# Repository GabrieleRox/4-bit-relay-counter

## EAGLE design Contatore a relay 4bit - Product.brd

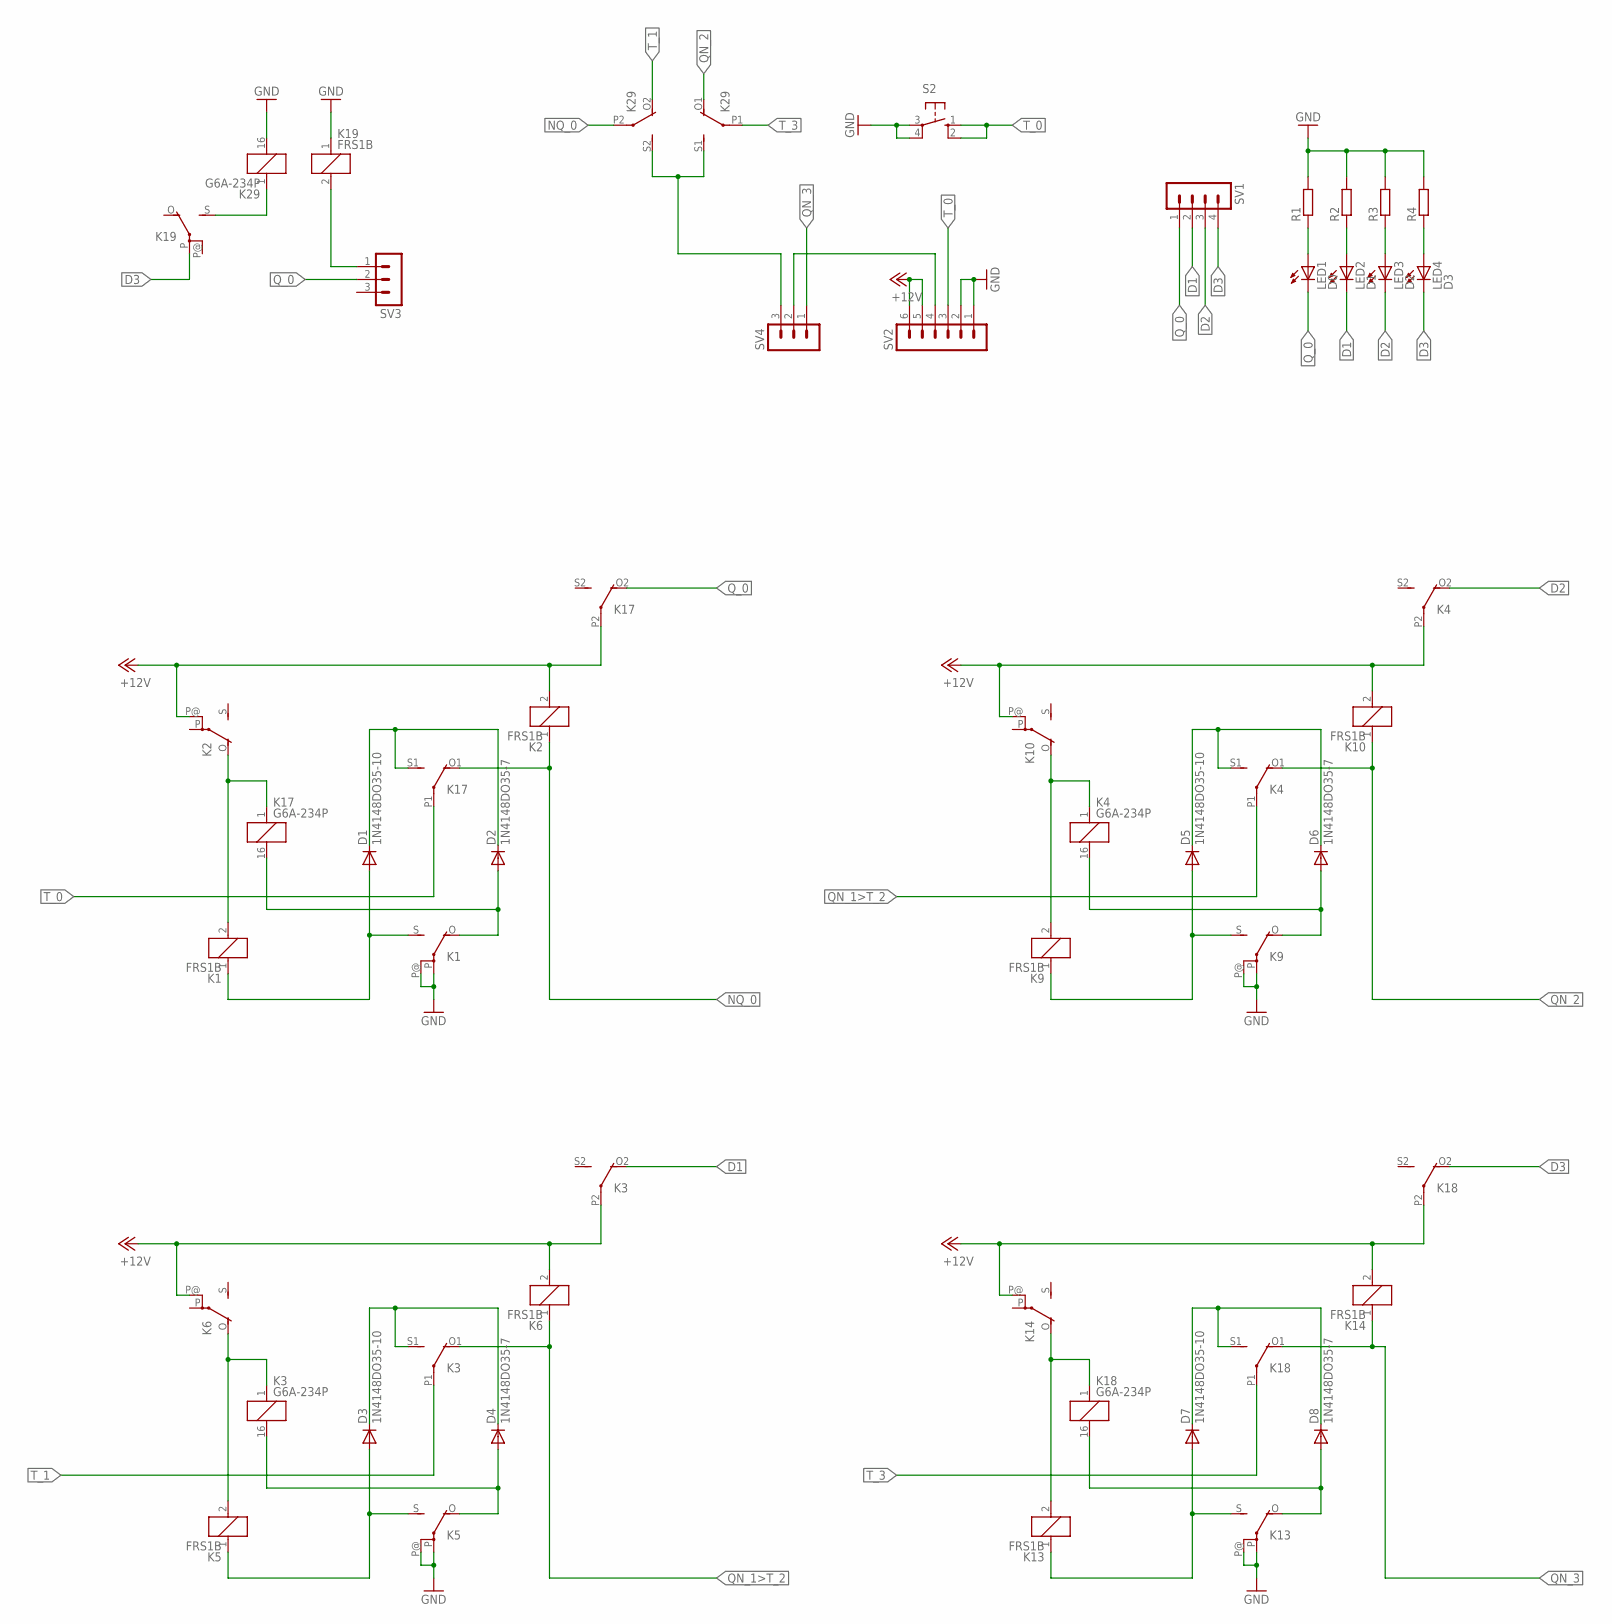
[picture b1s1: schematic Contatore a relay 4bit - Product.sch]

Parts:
D1, D3, D5, D7: 1N4148DO35-10; DO35-10
D2, D4, D6, D8: 1N4148DO35-7; DO35-7
K1, K2, K5, K6, K9, K10, K13, K14, K19: FRS1B
K3, K4, K17, K18, K29: G6A-234P
LED1: D0; LED3MM
LED2: D1; LED3MM
LED3: D2; LED3MM
LED4: D3; LED3MM
R1, R2, R3, R4: R-EU_M0805; M0805
S2: 10-XX; B3F-10XX
SV1: MA04-1
SV2: MA06-1
SV3, SV4: MA03-1

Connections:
+12V: K2.2, K2.P@, K3.P2, K4.P2, K6.2, K6.P@, K10.2, K10.P@, K14.2, K14.P@, K17.P2, K18.P2, SV2.5, SV2.6
D1: K3.O2 (O), LED2.K (C), SV1.2
D2: K4.O2 (O), LED3.K (C), SV1.3
D3: K18.O2 (O), K19.P, LED4.K (C), SV1.4
GND: K1.P, K1.P@, K5.P, K5.P@, K9.P, K9.P@, K13.P, K13.P@, K19.1, K29.16 (2), R1.2, R2.2, R3.2, R4.2, S2.3, S2.4 (P1), SV2.1, SV2.2
unnamed: D2.A, K1.O, K17.16 (2)
unnamed: D4.A, K3.16 (2), K5.O
unnamed: D1.A, K1.1, K1.S
unnamed: D3.A, K5.1, K5.S
unnamed: K3.1, K5.2, K6.O
unnamed: K1.2, K2.O, K17.1
unnamed: D3.C, D4.C, K3.S1 (S)
unnamed: D6.A, K4.16 (2), K9.O
unnamed: D5.A, K9.1, K9.S
unnamed: K4.1, K9.2, K10.O
unnamed: D1.C, D2.C, K17.S1 (S)
unnamed: D5.C, D6.C, K4.S1 (S)
unnamed: K29.S1 (S), K29.S2 (S), SV4.3
unnamed: D8.A, K13.O, K18.16 (2)
unnamed: D7.A, K13.1, K13.S
unnamed: K13.2, K14.O, K18.1
unnamed: LED1.A, R1.1
unnamed: D7.C, D8.C, K18.S1 (S)
unnamed: K19.S, K29.1
unnamed: LED2.A, R2.1
unnamed: LED3.A, R3.1
unnamed: LED4.A, R4.1
unnamed: K19.2, SV3.1
unnamed: SV2.4, SV4.2
NQ_0: K2.1, K17.O1 (O), K29.P2
QN_1>T_2: K3.O1 (O), K4.P1, K6.1
QN_2: K4.O1 (O), K10.1, K29.O1 (O)
QN_3: K14.1, K18.O1 (O), SV4.1
Q_0: K17.O2 (O), LED1.K (C), SV1.1, SV3.2
T_0: K17.P1, S2.1 (S), S2.2 (S1), SV2.3
T_1: K3.P1, K29.O2 (O)
T_3: K18.P1, K29.P1

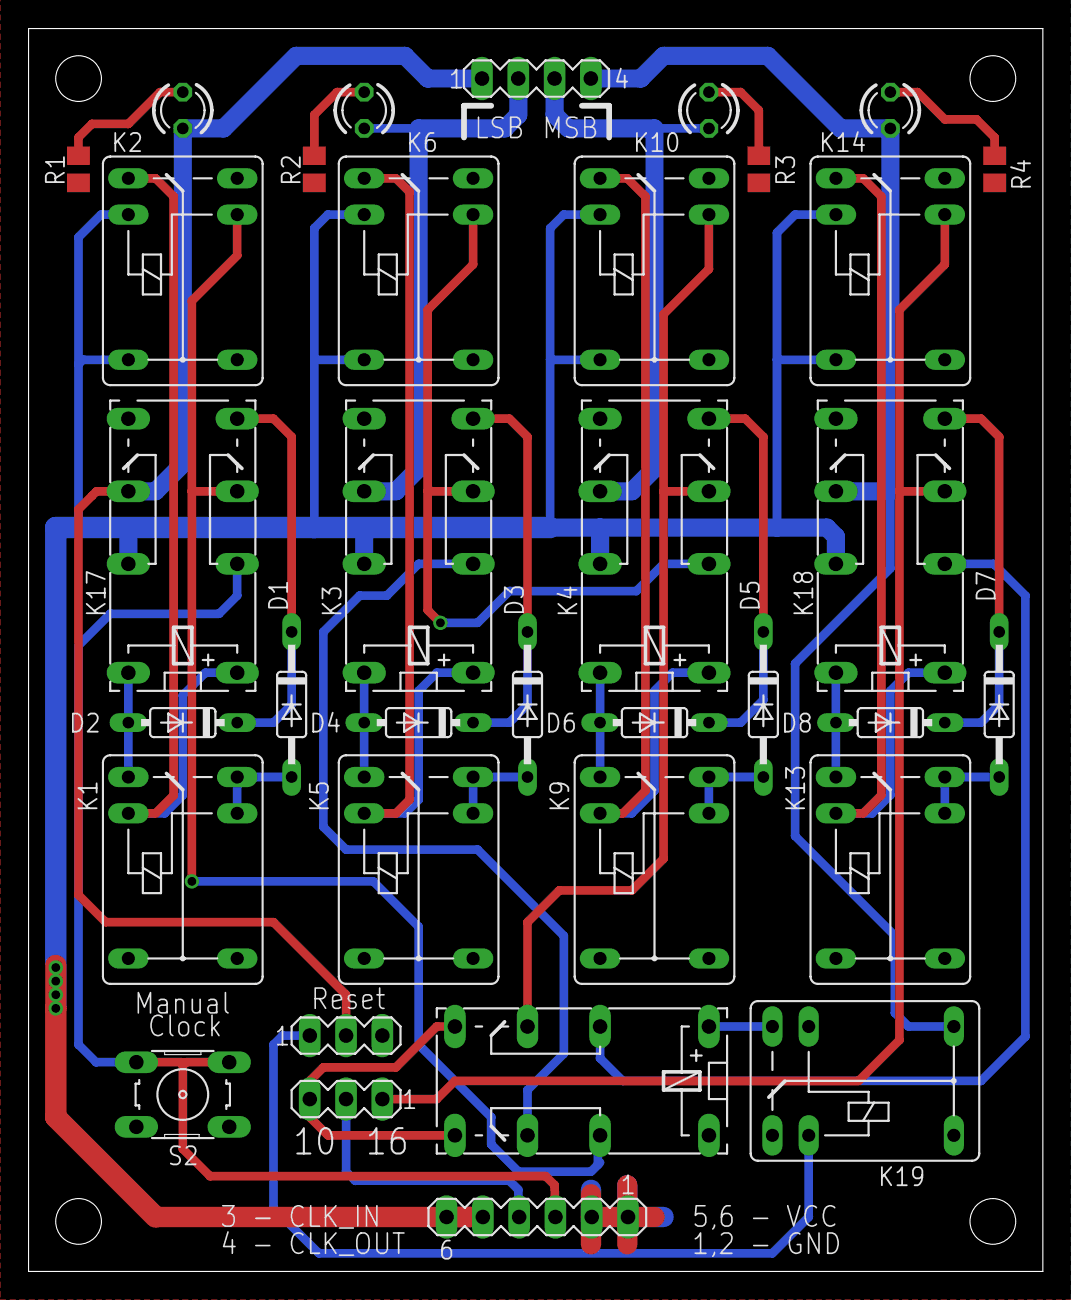
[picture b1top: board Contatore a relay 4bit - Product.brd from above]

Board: 2 copper layers, 71.0 x 87.0 mm, 35 parts (0 on the bottom side), 37 nets.

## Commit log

2022-02-11 First upload
2022-02-11 Create Board
